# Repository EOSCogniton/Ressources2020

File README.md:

# Ressources2020
Ce Git centralise tous les documents relatifs à la saison 2020 (diapos de Top, documentation, etc)

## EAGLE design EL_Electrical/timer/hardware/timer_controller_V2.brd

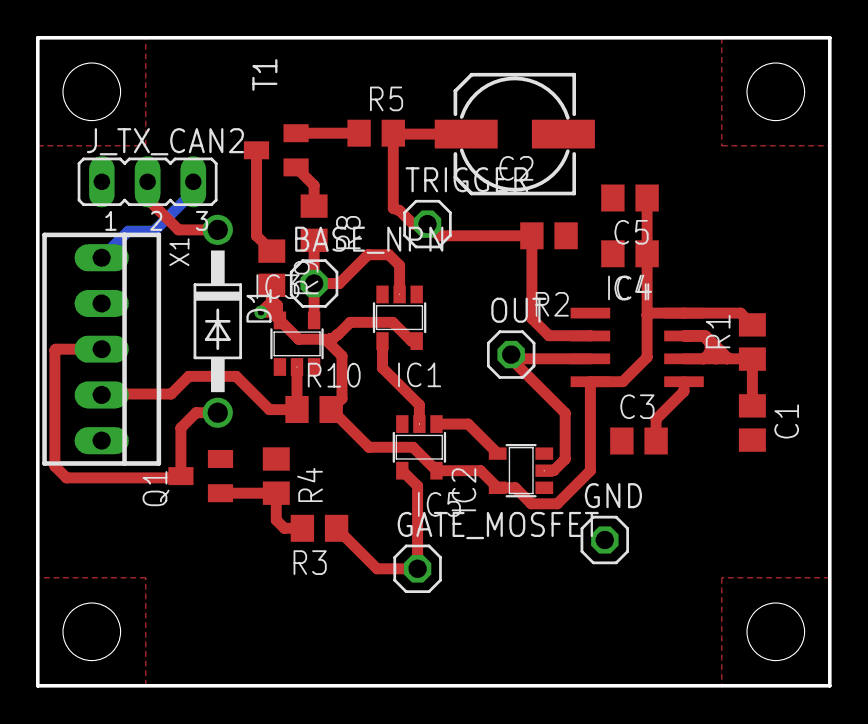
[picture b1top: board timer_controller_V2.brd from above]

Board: 2 copper layers, 44.0 x 36.0 mm, 28 parts (0 on the bottom side), 18 nets.

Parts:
BASE_NPN: BASE_NPN; 1X01
C1: 2.2µF; C0805
C2: 150µF; 153CLV-0605
C3: 0.01µF; C0805
C4: 0.1µF; C0805
C5: 1µF; C0805
D1: 1N4007; DO41-10
GATE_MOSFET: GATE_MOSFET; 1X01
GND: GND; 1X01
IC1, IC2, IC3: TC4S584F; SOT23-5
IC4: LM555D; SO08
IC5: Gate OR; SOT23-5
J_TX_CAN2: JP2
OUT: OUT; 1X01
Q1: BSS138; SOT23
R1: 2.2k; R0805
R2: 18k; R0805
R3, R4: 10k; R0805
R5: 12k; R0805
R8, R9: 100; R0805
R10: 1k; R0805
T1: 2N2369; SOT23
TRIGGER: TRIGGER; 1X01
X1: 22-23-2051

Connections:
12_SWITCHES: J_TX_CAN2.3, X1.1
+12V: C4.1, C5.1, IC1.5, IC2.5, IC3.5, IC4.4, IC4.8, IC5.5, J_TX_CAN2.1, R1.2, R9.2, R10.2, X1.2
BASE_NPN: BASE_NPN.1, IC1.2, IC3.4, R8.2
BP_START: IC3.2, R10.1, X1.4
GATE_MOSFET: GATE_MOSFET.1, IC5.4, R3.1
GND: C1.2, C2.-, C3.1, C4.2, C5.2, GND.1, IC1.3, IC2.3, IC3.3, IC4.1, IC5.3, Q1.2, R2.1, R4.1, X1.5
unnamed: Q1.1, R3.2, R4.2
unnamed: R9.1, T1.3
unnamed: IC1.4, IC5.2
unnamed: IC2.4, IC5.1
unnamed: C3.2, IC4.5
unnamed: C1.1, IC4.6, IC4.7, R1.1
unnamed: R5.1, T1.2
unnamed: R8.1, T1.1
OUT: IC2.2, IC4.3, OUT.1
RELAIS_INJECTEUR_12_PROTEGE: D1.C, J_TX_CAN2.2
RELAIS_INJECTEUR_MASSE: D1.A, Q1.3, X1.3
TRIGGER: C2.+, IC4.2, R2.2, R5.2, TRIGGER.1

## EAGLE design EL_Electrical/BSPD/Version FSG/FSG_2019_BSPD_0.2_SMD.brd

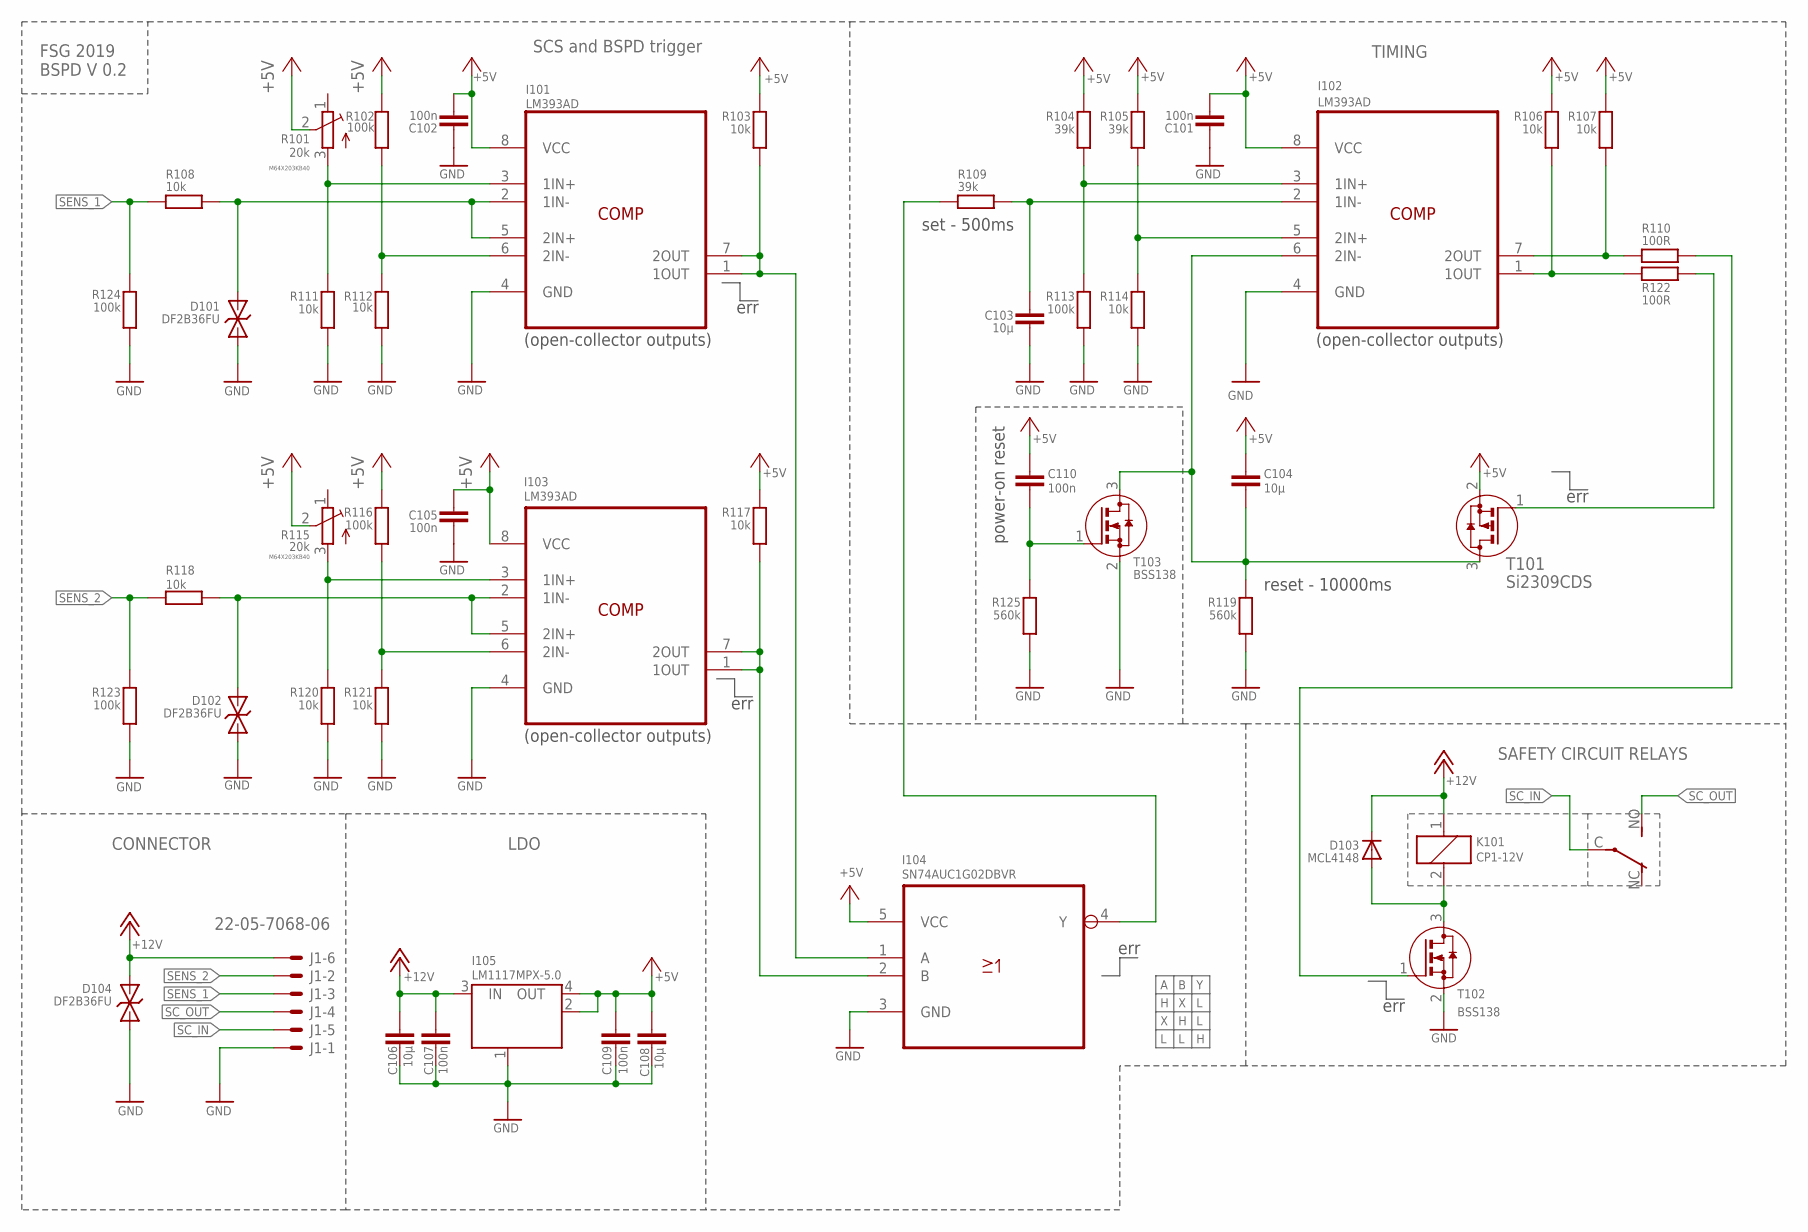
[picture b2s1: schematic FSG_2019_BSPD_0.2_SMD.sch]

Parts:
C101, C102, C105, C107, C109, C110: 100n; C0603
C103, C106, C108: 10µ; C1206
C104: 10µ; C1206K
D101, D102, D104: DF2B36FU; SOD323
D103: MCL4148; MICROMELF
I101, I102, I103: LM393AD; SOIC127P600X175-8N
I104: SN74AUC1G02DBVR; SOT95P280X145-5N
I105: LM1117MPX-5.0; LINEAR_SOT223
J1: 22-05-7068-06; 7395-06
K101: CP1-12V; CP1
R101, R115: 20k; M64X201KB40
R102, R113, R116, R123, R124: 100k; R0603
R103, R106, R107, R108, R111, R112, R114, R117, R118, R120, R121: 10k; R0603
R104, R105, R109: 39k; R0603
R110, R122: 100R; R0603
R119, R125: 560k; R0603
T101: Si2309CDS; SOT-23
T102, T103: BSS138; SOT-23

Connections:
+5V: C101.2, C102.2, C104.1, C105.2, C108.1, C109.2, C110.1, I101.8 (VCC), I102.8 (VCC), I103.8 (VCC), I104.5 (VCC), I105.2 (OUT), I105.4 (OUT), R101.2 (M), R102.1, R103.1, R104.2, R105.2, R106.2, R107.2, R115.2 (M), R116.1, R117.1, T101.2 (S)
+12V: C106.1, C107.1, D103.C, D104.2 (C), I105.3 (IN), J1.6, K101.1
BRAKE_F: D101.2 (C), I101.2 (1IN-), I101.5 (2IN+), R108.2
DF: D102.2 (C), I103.2 (1IN-), I103.5 (2IN+), R118.2
GND: C101.1, C102.1, C103.2, C105.1, C106.2, C107.2, C108.2, C109.1, D101.1 (A), D102.1 (A), D104.1 (A), I101.4 (GND), I102.4 (GND), I103.4 (GND), I104.3 (GND), I105.1 (GND/ADJ), J1.1, R111.2, R112.2, R113.1, R114.1, R119.1, R120.2, R121.2, R123.1, R124.1, R125.1, T102.2 (S), T103.2 (S)
unnamed: I102.5 (2IN+), R105.1, R114.2
unnamed: I103.1 (1OUT), I103.7 (2OUT), I104.2 (B), R117.2
unnamed: I101.1 (1OUT), I101.7 (2OUT), I104.1 (A), R103.2
unnamed: I102.1 (1OUT), R106.1, R122.2
unnamed: C110.2, R125.2, T103.1 (G)
unnamed: I101.3 (1IN+), R101.3 (A), R111.1
unnamed: C104.2, I102.6 (2IN-), R119.2, T101.3 (D), T103.3 (D)
unnamed: I103.3 (1IN+), R115.3 (A), R120.1
unnamed: R110.1, T102.1 (G)
unnamed: D103.A, K101.2, T102.3 (D)
unnamed: C103.1, I102.2 (1IN-), R109.1
unnamed: I102.3 (1IN+), R104.1, R113.2
unnamed: I101.6 (2IN-), R102.2, R112.1
unnamed: I102.7 (2OUT), R107.1, R110.2
unnamed: I103.6 (2IN-), R116.2, R121.1
unnamed: R122.1, T101.1 (G)
unnamed: I104.4 (Y), R109.2
SC_IN: J1.5, K101.C
SC_OUT: J1.4, K101.NO (S)
SENS_1: J1.3, R108.1, R124.2
SENS_2: J1.2, R118.1, R123.2

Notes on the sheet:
COMP
M64X203KB40
FSG 2019 BSPD V 0.2
CONNECTOR
LDO
SAFETY CIRCUIT RELAYS
err
TIMING
SCS and BSPD trigger
power-on reset
set - 500ms
reset - 10000ms
(open-collector outputs)

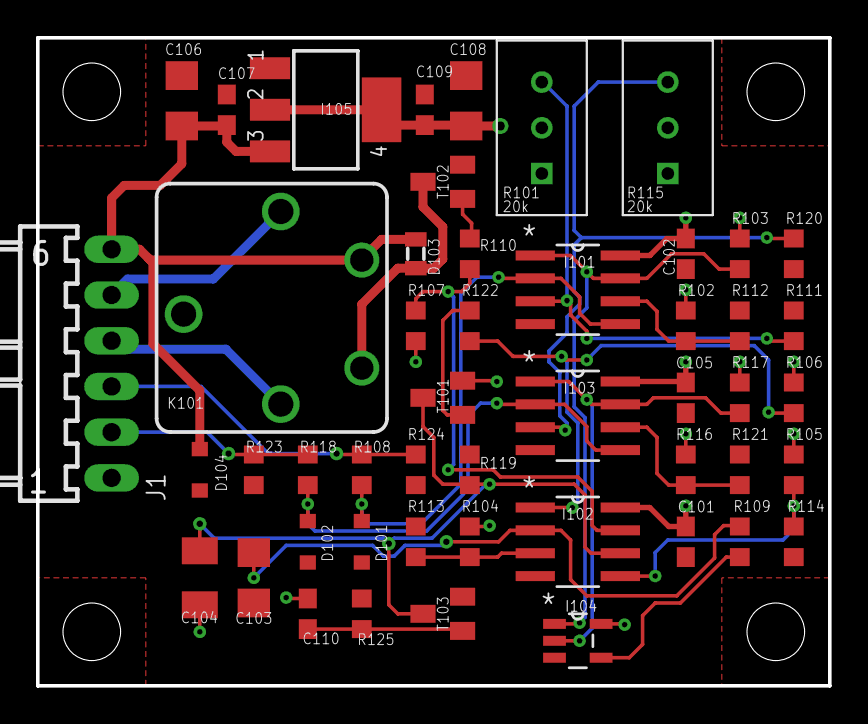
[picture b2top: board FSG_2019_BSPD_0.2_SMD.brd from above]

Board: 2 copper layers, 44.0 x 36.0 mm, 49 parts (0 on the bottom side), 26 nets.

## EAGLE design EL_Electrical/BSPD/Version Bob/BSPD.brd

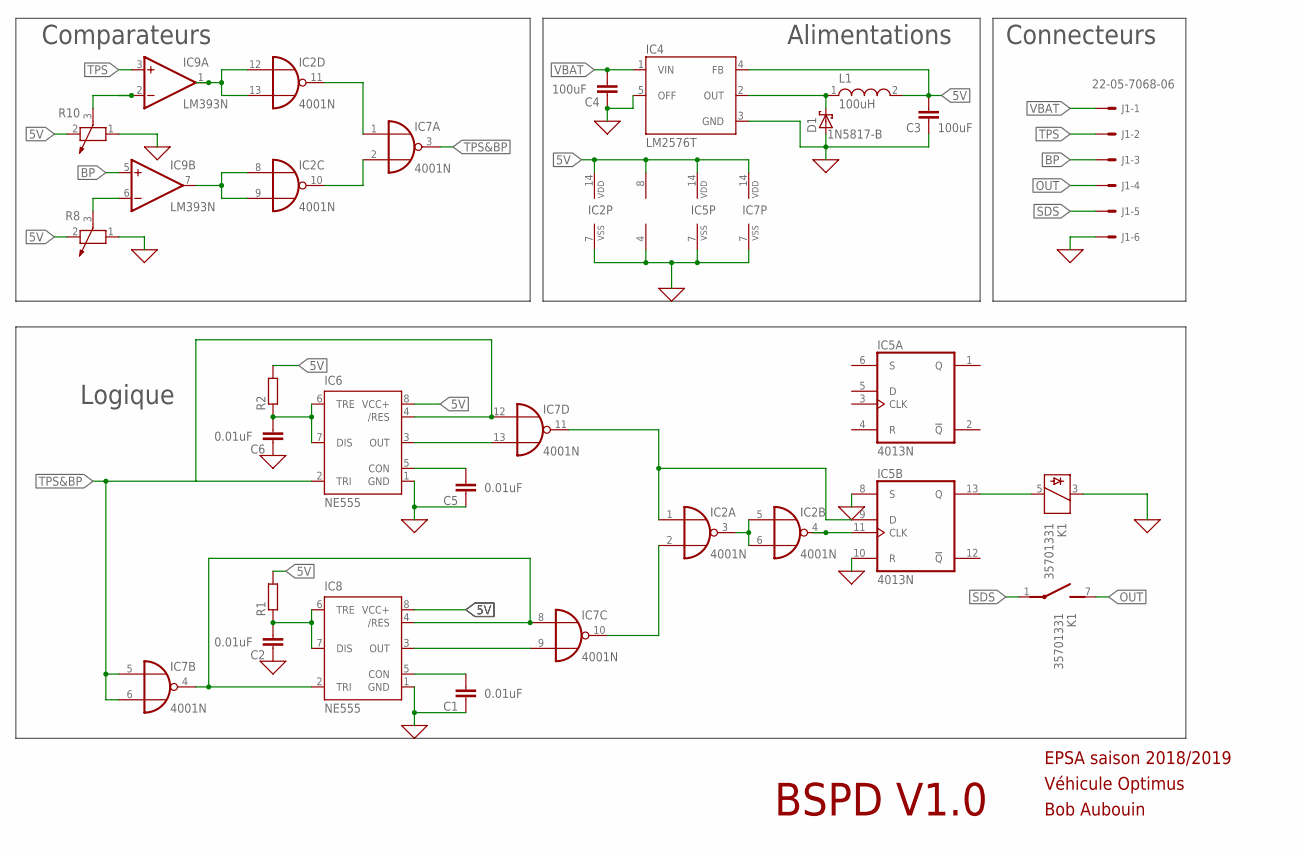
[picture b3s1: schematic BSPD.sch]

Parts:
C1, C2, C5, C6: 0.01uF; C025-025X050
C3, C4: 100uF; C025-025X050
D1: 1N5817-B; DO41-7.6
IC2, IC7: 4001N; DIL14
IC4: LM2576T; TO220-5
IC5: 4013N; DIL14
IC6, IC8: NE555; DIL-08
IC9: LM393N; DIL08
J1: 22-05-7068-06; 7395-06
K1: 35701331; REED
L1: 100uH; WE-TI_8012
R1, R2: R-EU_0207/10; 0207/10
R8, R10: POTENTIOMETER_PT_SPIN; PT-SPIN

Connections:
0: C1.1, C2.1, C3.1, C4.1, C5.1, C6.1, D1.A, IC2.7 (VSS), IC4.3 (GND), IC4.5 (OFF), IC5.7 (VSS), IC5.8 (S), IC5.10 (R), IC6.1 (GND), IC7.7 (VSS), IC8.1 (GND), IC9.4 (V-), J1.6, K1.3, R8.1, R10.1
5V: C3.2, IC2.14 (VDD), IC4.4 (FB), IC5.14 (VDD), IC6.8 (VCC+), IC7.14 (VDD), IC8.8 (VCC+), IC9.8 (V+), L1.2, R1.2, R2.2, R8.2, R10.2
BP: IC9.5 (+IN), J1.3
unnamed: C1.2, IC8.5 (CON)
unnamed: IC7.4 (O), IC7.8 (I0), IC8.2 (TRI), IC8.4 (/RES)
unnamed: C2.2, IC8.6 (TRE), IC8.7 (DIS), R1.1
unnamed: IC7.9 (I1), IC8.3 (OUT)
unnamed: C6.2, IC6.6 (TRE), IC6.7 (DIS), R2.1
unnamed: C5.2, IC6.5 (CON)
unnamed: IC2.12 (I0), IC2.13 (I1), IC9.1 (OUT)
unnamed: IC2.2 (I1), IC7.10 (O)
unnamed: IC2.1 (I0), IC5.9 (D), IC7.11 (O)
unnamed: IC2.4 (O), IC5.11 (CLK)
unnamed: IC6.3 (OUT), IC7.13 (I1)
unnamed: IC5.13 (Q), K1.5
unnamed: IC9.2 (-IN), R10.3
unnamed: IC9.6 (-IN), R8.3
unnamed: IC2.8 (I0), IC2.9 (I1), IC9.7 (OUT)
unnamed: D1.C, IC4.2 (OUT), L1.1
unnamed: IC2.11 (O), IC7.1 (I0)
unnamed: IC2.10 (O), IC7.2 (I1)
unnamed: IC2.3 (O), IC2.5 (I0), IC2.6 (I1)
OUT: J1.4, K1.7 (S)
SDS: J1.5, K1.1
TPS: IC9.3 (+IN), J1.2
TPS&BP: IC6.2 (TRI), IC6.4 (/RES), IC7.3 (O), IC7.5 (I0), IC7.6 (I1), IC7.12 (I0)
VBAT: C4.2, IC4.1 (VIN), J1.1

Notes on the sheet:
BSPD V1.0
EPSA saison 2018/2019
Véhicule Optimus
Bob Aubouin
Logique
Comparateurs
Alimentations
Connecteurs

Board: 2 copper layers, 21 parts (0 on the bottom side), 27 nets, no tracks yet.

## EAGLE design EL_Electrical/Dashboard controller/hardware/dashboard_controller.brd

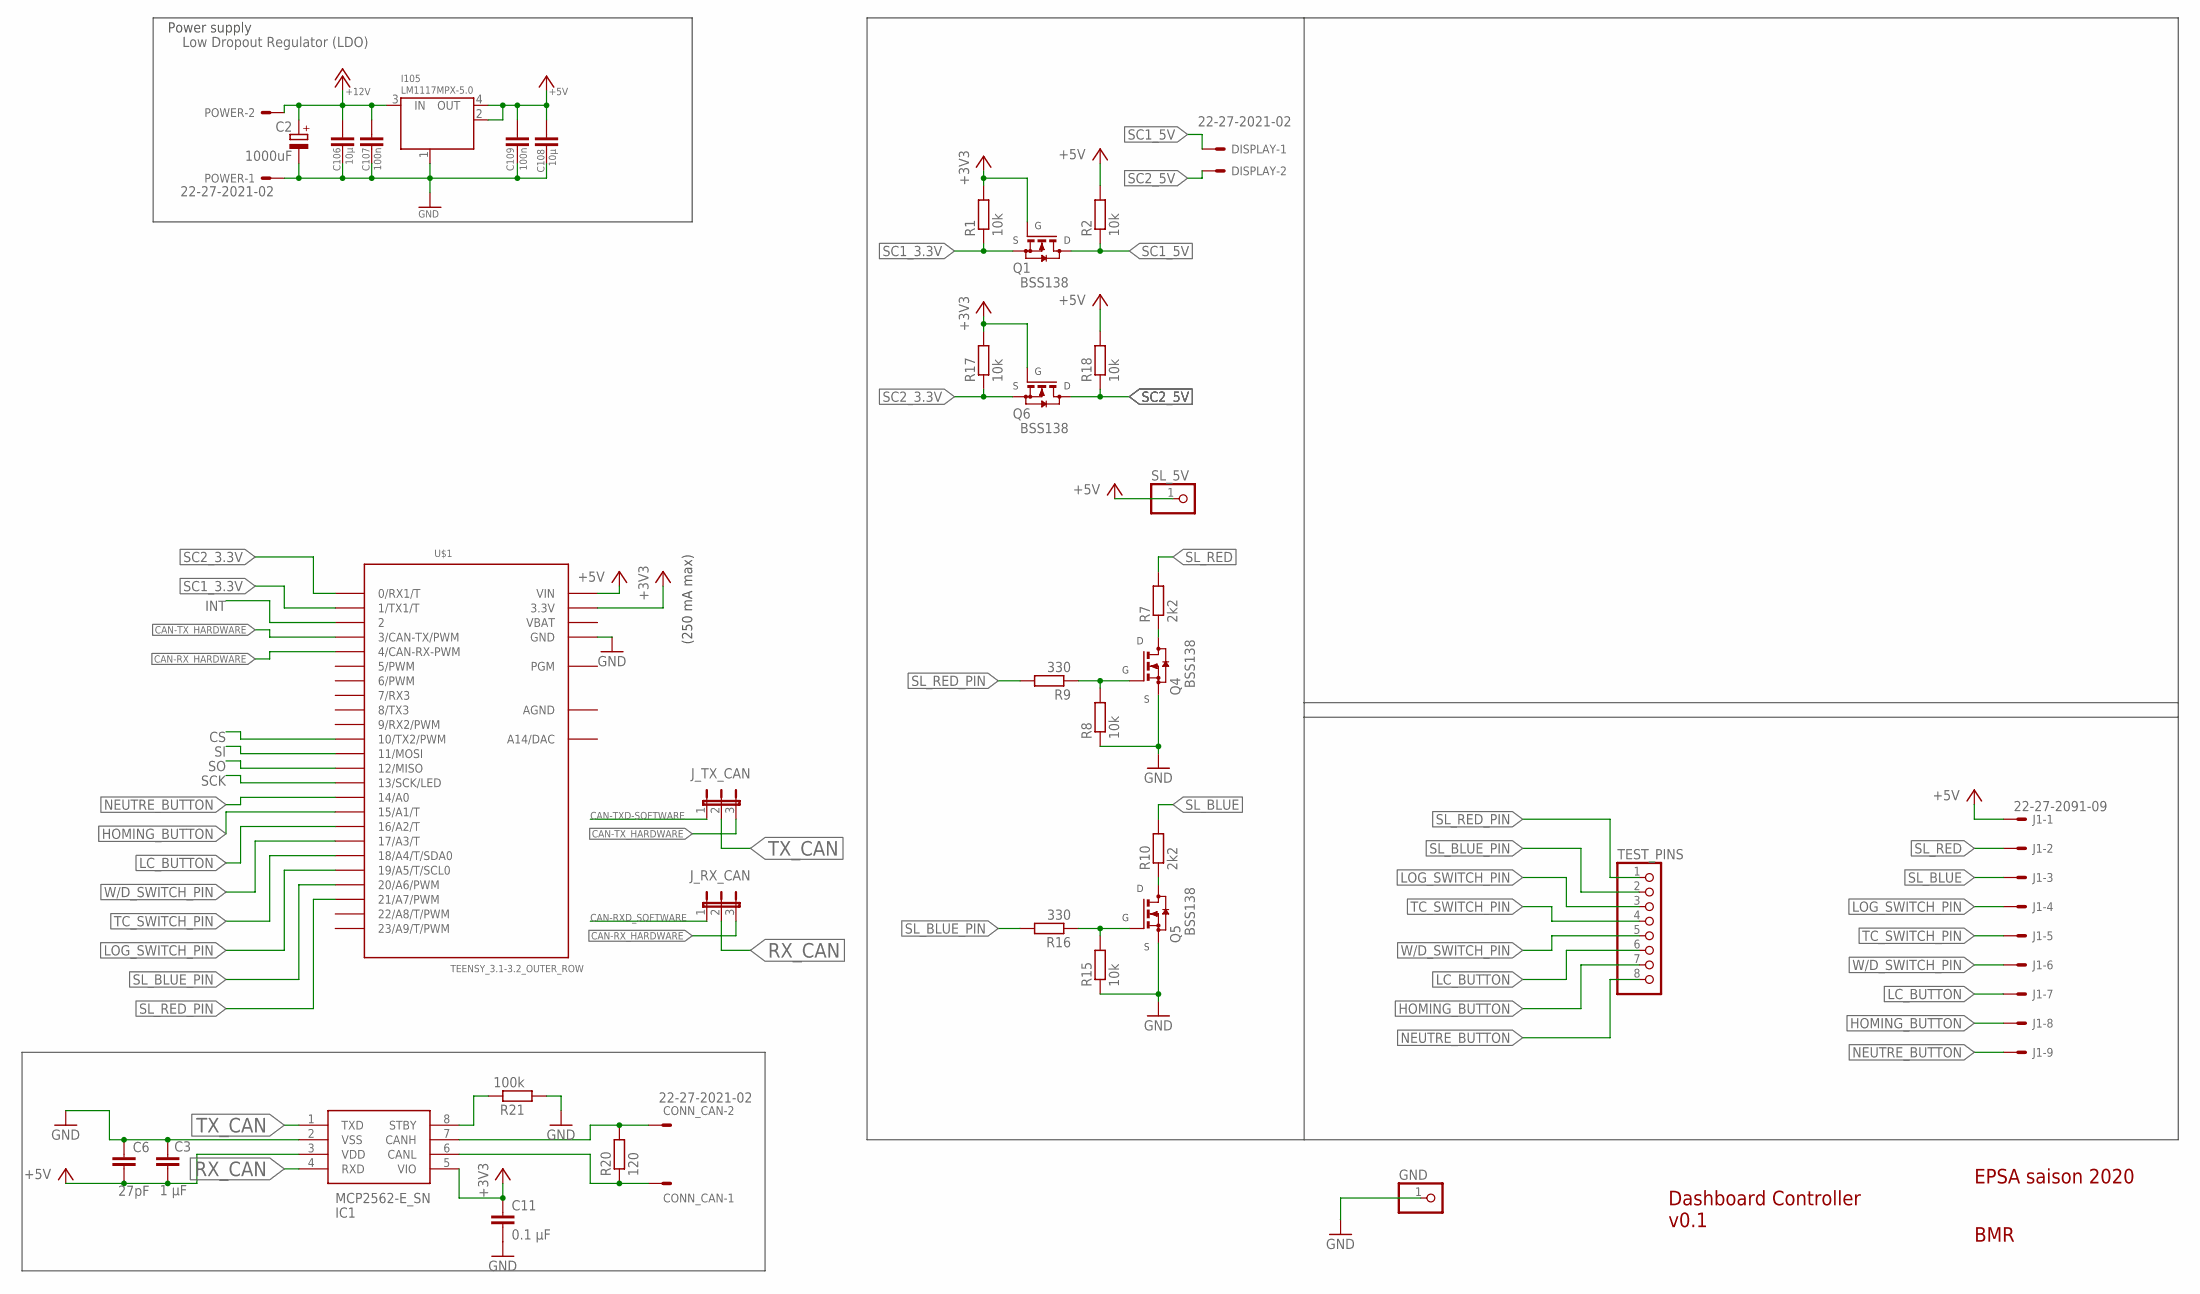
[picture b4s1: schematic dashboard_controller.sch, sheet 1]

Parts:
C2: 1000uF; E25-10
C3: 1 µF; C0805
C6: 27pF; C0805
C11: 0.1 µF; C0805
C106, C108: 10µ; C0805
C107, C109: 100n; C0603
CONN_CAN: 22-27-2021-02; 6410-02
DISPLAY: 22-27-2021-02; 6410-02
GND: PINHD-1X1; 1X01
I105: LM1117MPX-5.0; LINEAR_SOT223
IC1: MCP2562-E_SN; SOIC127P600X175-8N
J1: 22-27-2091-09; 6410-09
J_RX_CAN: JP2E; JP2
J_TX_CAN: JP2E; JP2
POWER: 22-27-2021-02; 6410-02
Q1, Q4, Q5, Q6: BSS138; SOT23
R1, R2, R8, R15, R17, R18: 10k; R0805
R7, R10: 2k2; R0805
R9, R16: 330; R0805
R20: 120; R0805
R21: 100k; R0805
SL_5V: PINHD-1X1; 1X01
TEST_PINS: PINHD-1X8; 1X08
U$1: TEENSY_3.1-3.2_OUTER_ROW; TEENSY_3.0-3.2&LC_OUTER_ROW

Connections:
+3V3: C11.1, IC1.5 (VIO), Q1.1 (G), Q6.1 (G), R1.2, R17.2, U$1.3.3V, U$1.3.3V1 (3.3V); also elsewhere on the board
+5V: C3.2, C6.2, C108.1, C109.2, I105.2 (OUT), I105.4 (OUT), IC1.3 (VDD), J1.1, R2.2, R18.2, SL_5V.1, U$1.VIN
+12V: C2.+, C106.1, C107.1, I105.3 (IN), POWER.2
AGND: U$1.AGND
CAN-RXD_SOFTWARE: J_RX_CAN.1; also elsewhere on the board
CAN-RX_HARDWARE: J_RX_CAN.3, U$1.4 (4/CAN-RX-PWM)
CAN-TXD-SOFTWARE: J_TX_CAN.1; also elsewhere on the board
CAN-TX_HARDWARE: J_TX_CAN.3, U$1.3 (3/CAN-TX/PWM)
CS: U$1.10 (10/TX2/PWM); also elsewhere on the board
GND: C2.-, C3.1, C6.1, C11.2, C106.2, C107.2, C108.2, C109.1, GND.1, I105.1 (GND/ADJ), IC1.2 (VSS), POWER.1, Q4.2 (S), Q5.2 (S), R8.1, R15.1, R21.1, U$1.GND, U$1.GND1 (GND); also elsewhere on the board
HOMING_BUTTON: J1.8, TEST_PINS.7, U$1.15/A1 (15/A1/T)
INT: U$1.2; also elsewhere on the board
LC_BUTTON: J1.7, TEST_PINS.6, U$1.16/A2 (16/A2/T)
LOG_SWITCH_PIN: J1.4, TEST_PINS.3, U$1.19/A5 (19/A5/T/SCL0)
unnamed: CONN_CAN.2, IC1.7 (CANH), R20.2
unnamed: IC1.8 (STBY), R21.2
unnamed: Q4.3 (D), R7.1
unnamed: Q5.1 (G), R15.2, R16.1
unnamed: CONN_CAN.1, IC1.6 (CANL), R20.1
unnamed: Q4.1 (G), R8.2, R9.1
unnamed: Q5.3 (D), R10.1
NEUTRE_BUTTON: J1.9, TEST_PINS.8, U$1.14/A0
RX_CAN: IC1.4 (RXD), J_RX_CAN.2
SC1_3.3V: Q1.2 (S), R1.1, U$1.1 (1/TX1/T)
SC1_5V: DISPLAY.1, Q1.3 (D), R2.1
SC2_3.3V: Q6.2 (S), R17.1, U$1.0 (0/RX1/T)
SC2_5V: DISPLAY.2, Q6.3 (D), R18.1
SCK: U$1.13 (13/SCK/LED); also elsewhere on the board
SI: U$1.11 (11/MOSI); also elsewhere on the board
SL_BLUE: J1.3, R10.2
SL_BLUE_PIN: R16.2, TEST_PINS.2, U$1.20/A6 (20/A6/PWM)
SL_RED: J1.2, R7.2
SL_RED_PIN: R9.2, TEST_PINS.1, U$1.21/A7 (21/A7/PWM)
SO: U$1.12 (12/MISO); also elsewhere on the board
TC_SWITCH_PIN: J1.5, TEST_PINS.4, U$1.18/A4 (18/A4/T/SDA0)
TX_CAN: IC1.1 (TXD), J_TX_CAN.2
VBAT: U$1.VBAT
W/D_SWITCH_PIN: J1.6, TEST_PINS.5, U$1.17/A3 (17/A3/T)

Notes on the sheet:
Dashboard Controller v0.1
EPSA saison 2020
BMR
(250 mA max)
Low Dropout Regulator (LDO)
Power supply

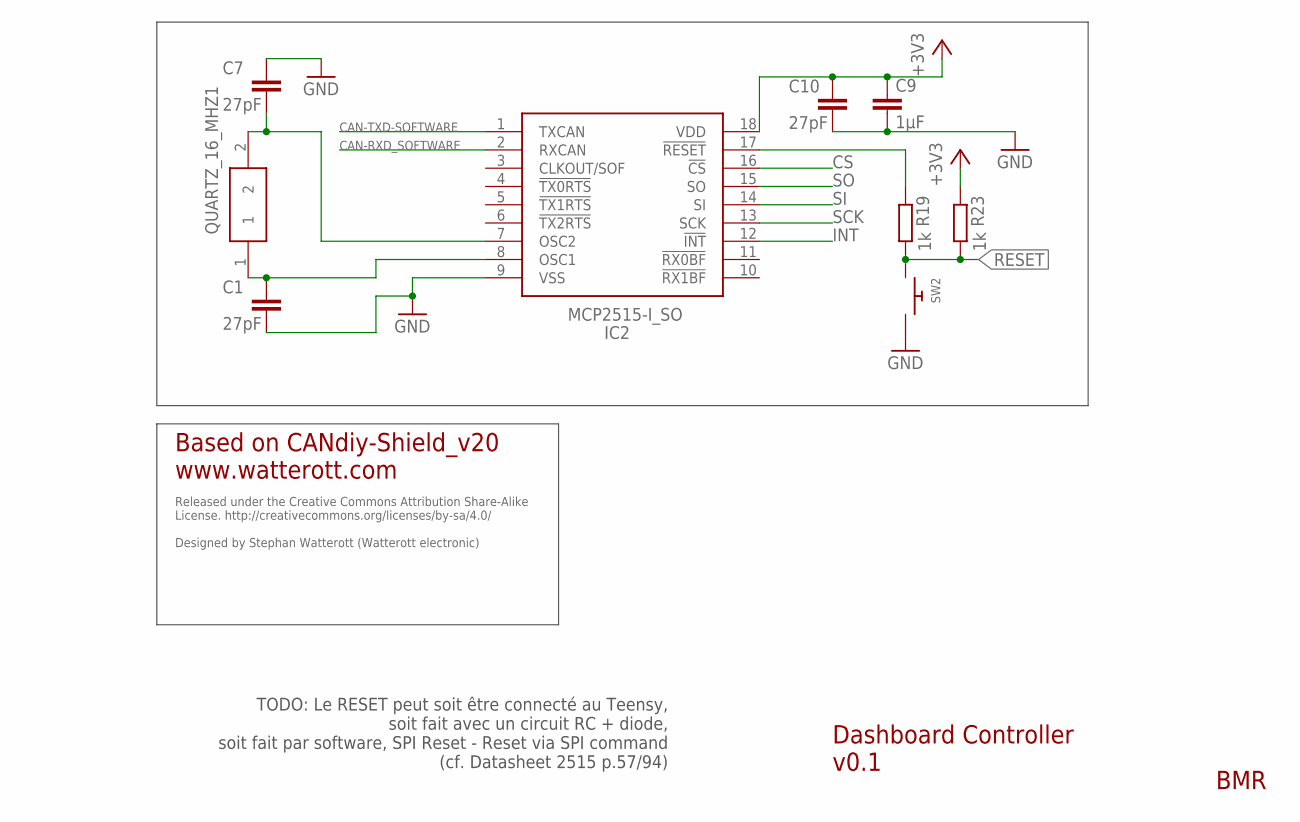
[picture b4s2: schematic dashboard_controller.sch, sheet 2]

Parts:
C1, C7, C10: 27pF; C0805
C9: 1µF; C0805
IC2: MCP2515-I_SO; SOIC127P1030X265-18N
QUARTZ_16_MHZ1: FOXSLF_160-20; HC49SLF_1
R19, R23: 1k; R0805
SW2: SWITCH_PUSHBUTTONEVQ-PE; TACT_PANA-EVQ

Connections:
+3V3: C9.1, C10.1, IC2.18 (VDD), R23.1; also elsewhere on the board
CAN-RXD_SOFTWARE: IC2.2 (RXCAN); also elsewhere on the board
CAN-TXD-SOFTWARE: IC2.1 (TXCAN); also elsewhere on the board
CS: IC2.16 (!CS); also elsewhere on the board
GND: C1.2, C7.1, C9.2, C10.2, IC2.9 (VSS), SW2.P$2; also elsewhere on the board
INT: IC2.12 (!INT); also elsewhere on the board
unnamed: C1.1, IC2.8 (OSC1), QUARTZ_16_MHZ1.1
unnamed: C7.2, IC2.7 (OSC2), QUARTZ_16_MHZ1.2
unnamed: IC2.17 (!RESET), R19.1
RESET: R19.2, R23.2, SW2.P$1
SCK: IC2.13 (SCK); also elsewhere on the board
SI: IC2.14 (SI); also elsewhere on the board
SO: IC2.15 (SO); also elsewhere on the board

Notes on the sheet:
Dashboard Controller v0.1
BMR
Released under the Creative Commons Attribution Share-Alike License. http://creativecommons.org/licenses/by-sa/4.0/ Designed by Stephan Watterott (Watterott electronic)
Based on CANdiy-Shield_v20 www.watterott.com
TODO: Le RESET peut soit être connecté au Teensy, soit fait avec un circuit RC + diode, soit fait par software, SPI Reset - Reset via SPI command (cf. Datasheet 2515 p.57/94)

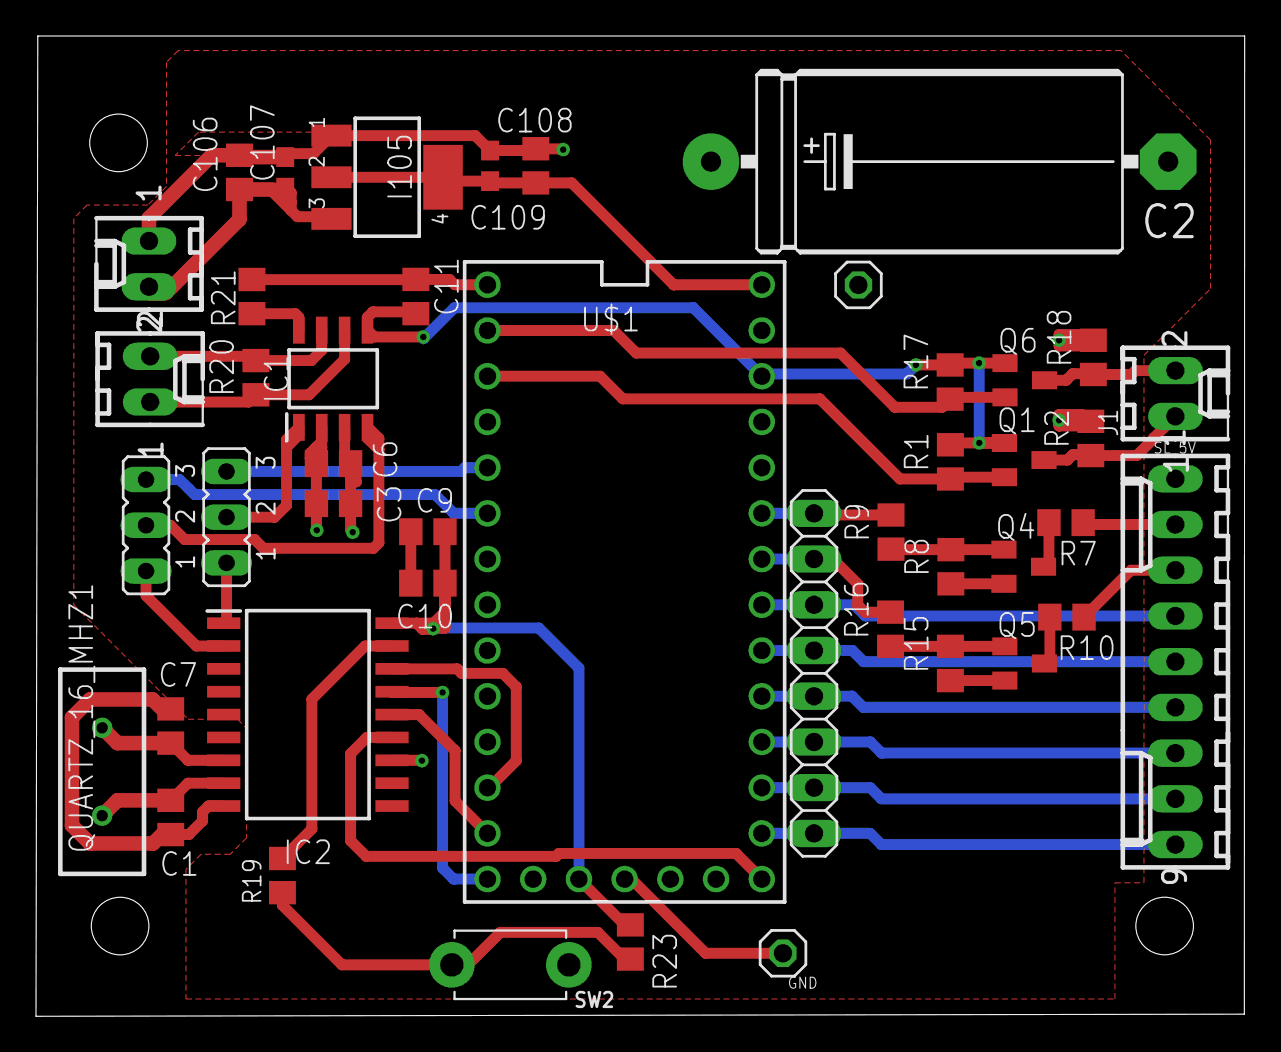
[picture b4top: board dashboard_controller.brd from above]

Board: 4 copper layers, 67.1 x 54.5 mm, 45 parts (0 on the bottom side), 40 nets.

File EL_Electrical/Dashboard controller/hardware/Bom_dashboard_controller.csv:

Qty;Value;Device;Package;Parts;Description;ALLIED_NUMBER;CASE;DESCRIPTION;HEIGHT;MANUFACTURER_NAME;MANUFACTURER_PART_NUMBER;MF;MONTHLY_USAGE;MPN;OC_FARNELL;OC_NEWARK;PART_NUMBER;POPULARITY;PRICE;RS_PART_NUMBER;SPICEPREFIX;SUPPLIER;TYPE;VALUE
2;;JP2E;JP2;J_RX_CAN, J_TX_CAN;JUMPER;;;;;;;;;;;;;34;;;;;;
2;;PINHD-1X1;1X01;GND, SL_5V;PIN HEADER;;;;;;;;;;;;;64;;;;;;
1;;PINHD-1X2;1X02;TEST_CAN;PIN HEADER;;;;;;;;;;;;;98;;;;;;
1;;PINHD-1X8;1X08;TEST_PINS;PIN HEADER;;;;;;;;;;;;;67;;;;;;
1;;SWITCH_PUSHBUTTONEVQ-PE;TACT_PANA-EVQ;SW2;Buttons;;;;;;;;;;;;;;;;;;;
1;0.1 µF;C-EUC0805;C0805;C11;CAPACITOR, European symbol;;;;;;;;;;;;;88;;;C;;;
1;1 µF;C-EUC0805;C0805;C3;CAPACITOR, European symbol;;;;;;;;;;;;;88;;;C;;;
1;1000uF;CPOL-EUE25-10AXIAL;E25-10;C2;POLARIZED CAPACITOR, European symbol;;;;;;;;;;;;;0;;;C;;;
1;100k;R-EU_R0805;R0805;R21;RESISTOR, European symbol;;;;;;;;;;;;;86;;;R;;;
2;100n;C-EUC0603;C0603;C107, C109;CAPACITOR, European symbol;;;;;;;;;;;;;;;;;;;
6;10k;R-EU_R0805;R0805;R1, R2, R8, R15, R17, R18;RESISTOR, European symbol;;;;;;;;;;;;;86;;;R;;;
2;10µ;C-EUC0805;C0805;C106, C108;CAPACITOR, European symbol;;;;;;;;;;;;;88;;;C;;;
1;120;R-EU_R0805;R0805;R20;RESISTOR, European symbol;;;;;;;;;;;;;86;;;R;;;
2;1k;R-EU_R0805;R0805;R19, R23;RESISTOR, European symbol;;;;;;;;;;;;;86;;;R;;;
1;1µF;C-EUC0805;C0805;C9;CAPACITOR, European symbol;;;;;;;;;;;;;88;;;C;;;
3;22-27-2021-02;22-27-2021-02;6410-02;ALIM, CONN_CAN, DISPLAY;CONNECTOR;;;;;;;MOLEX;;;unknown;unknown;;0;;;;;;
1;22-27-2091-09;22-27-2091-09;6410-09;J1;CONNECTOR;;;;;;;MOLEX;;;unknown;unknown;;0;;;;;;
4;27pF;C-EUC0805;C0805;C1, C6, C7, C10;CAPACITOR, European symbol;;;;;;;;;;;;;88;;;C;;;
2;2k2;R-EU_R0805;R0805;R7, R10;RESISTOR, European symbol;;;;;;;;;;;;;86;;;R;;;
2;330;R-EU_R0805;R0805;R9, R16;RESISTOR, European symbol;;;;;;;;;;;;;86;;;R;;;
4;BSS138;BSS123;SOT23;Q1, Q4, Q5, Q6;N-CHANNEL MOS FET;;;;;;;;;;;;;21;;;;;;
1;FOXSLF_160-20;FOXSLF_160-20;HC49SLF_1;QUARTZ_16_MHZ1;Crystal 16.000MHz HC49S HC-49-SLF Crystal 16MHz, ??30ppm, 2-Pin;;;Crystal 16.000MHz HC49S HC-49-SLF Crystal 16MHz, ??30ppm, 2-Pin;mm;Fox;FOXSLF/160-20;;;;;;;;;1734298;;;;
1;LM1117MPX-5.0;0022_LM1117IMPX-5.0;LINEAR_SOT223;I105;Low-dropout linear regulator 5V  -LM1117IMPX-5.0;;SOT223;;;;;;_____;;;;LM1117IMPX-5.0;;_____;;;_____;Circuito_Integrato;LM1117IMPX-5.0
1;MCP2515-I_SO;MCP2515-I_SO;SOIC127P1030X265-18N;IC2;CAN Controller SPI data filtering SO18;70045399;;CAN Controller SPI data filtering SO18;2.65mm;Microchip;MCP2515-I/SO;;;;;;;;;1445765;;;;
1;MCP2562-E_SN;MCP2562-E_SN;SOIC127P600X175-8N;IC1;CAN Transceiver 1Mbps 5V 125degC SOIC8 CAN Transceiver 1MBps IEC 61000-4-2 Standby-Mode 8pins SOIC;70415107;;CAN Transceiver 1Mbps 5V 125degC SOIC8 CAN Transceiver 1MBps IEC 61000-4-2 Standby-Mode 8pins SOIC;1.75mm;Microchip;MCP2562-E/SN;;;;;;;;;7990228P;;;;
1;TEENSY_3.1-3.2_OUTER_ROW;TEENSY_3.1-3.2_OUTER_ROW;TEENSY_3.0-3.2&LC_OUTER_ROW;U$1;Footprint for Teensy 3.1 or 3.2 board using all pin connections on the outer perimeter;;;;;;;;;;;;;;;;;;;

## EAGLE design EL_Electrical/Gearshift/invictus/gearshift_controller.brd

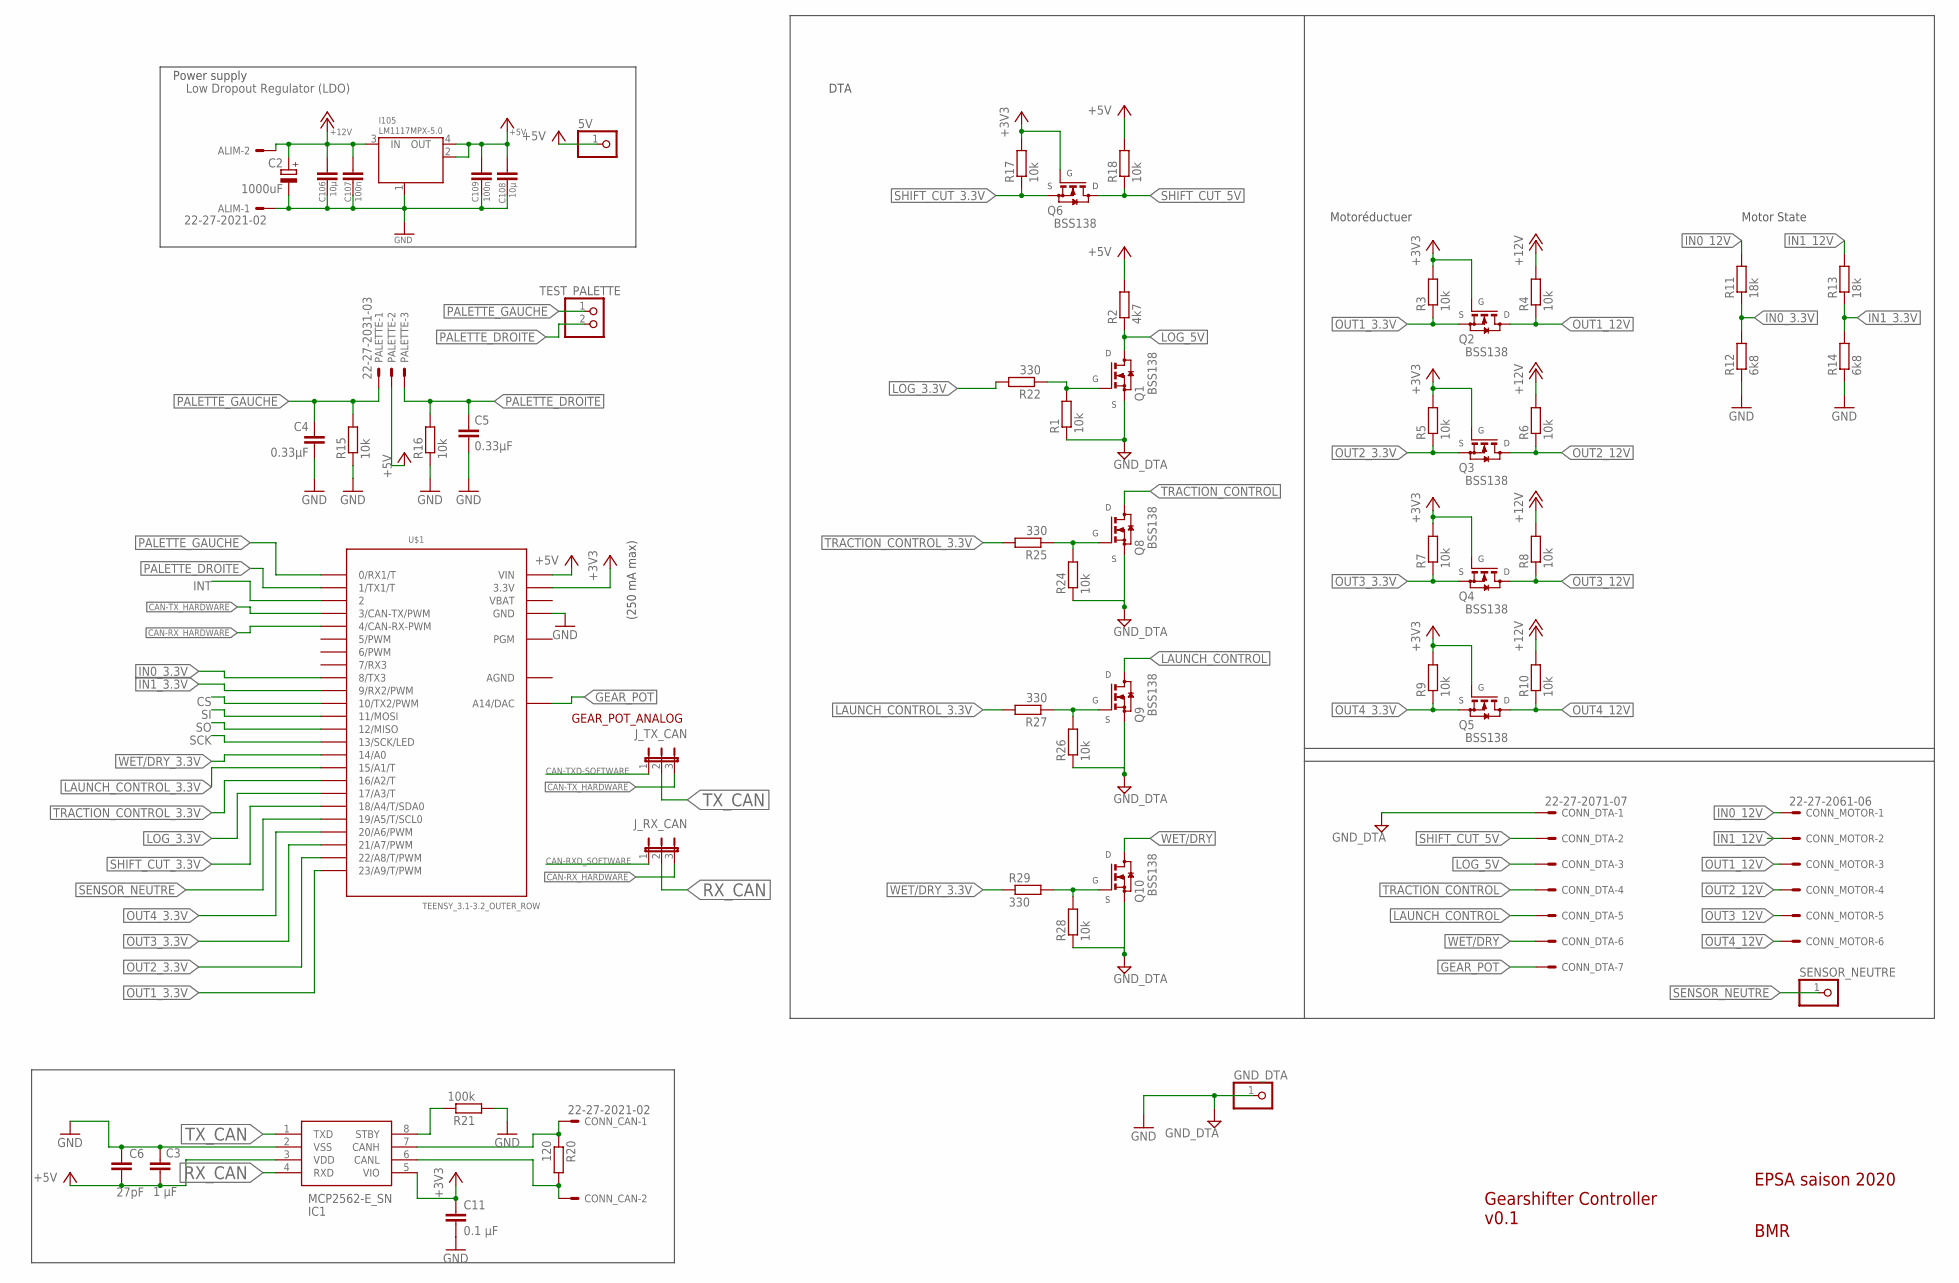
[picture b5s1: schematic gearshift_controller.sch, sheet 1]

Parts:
5V: PINHD-1X1; 1X01
ALIM: 22-27-2021-02; 6410-02
C2: 1000uF; E25-10
C3: 1 µF; C0805
C4, C5: 0.33µF; C0805
C6: 27pF; C0805
C11: 0.1 µF; C0805
C106, C108: 10µ; C0805
C107, C109: 100n; C0603
CONN_CAN: 22-27-2021-02; 6410-02
CONN_DTA: 22-27-2071-07; 6410-07
CONN_MOTOR: 22-27-2061-06; 6410-06
GND_DTA: PINHD-1X1; 1X01
I105: LM1117MPX-5.0; LINEAR_SOT223
IC1: MCP2562-E_SN; SOIC127P600X175-8N
J_RX_CAN: JP2E; JP2
J_TX_CAN: JP2E; JP2
PALETTE: 22-27-2031-03; 6410-03
Q1, Q2, Q3, Q4, Q5, Q6, Q8, Q9, Q10: BSS138; SOT23
R1, R3, R4, R5, R6, R7, R8, R9, R10, R15, R16, R17, R18, R24, R26, R28: 10k; R0805
R2: 4k7; R0805
R11, R13: 18k; R0805
R12, R14: 6k8; R0805
R20: 120; R0805
R21: 100k; R0805
R22, R25, R27, R29: 330; R0805
SENSOR_NEUTRE: PINHD-1X1; 1X01
TEST_PALETTE: PINHD-1X2; 1X02
U$1: TEENSY_3.1-3.2_OUTER_ROW; TEENSY_3.0-3.2&LC_OUTER_ROW

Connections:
+3V3: C11.1, IC1.5 (VIO), Q2.1 (G), Q3.1 (G), Q4.1 (G), Q5.1 (G), Q6.1 (G), R3.2, R5.2, R7.2, R9.2, R17.2, U$1.3.3V, U$1.3.3V1 (3.3V); also elsewhere on the board
+5V: 5V.1, C3.2, C6.2, C108.1, C109.2, I105.2 (OUT), I105.4 (OUT), IC1.3 (VDD), PALETTE.2, R2.2, R18.2, U$1.VIN
+12V: ALIM.2, C2.+, C106.1, C107.1, I105.3 (IN), R4.2, R6.2, R8.2, R10.2
AGND: U$1.AGND
CAN-RXD_SOFTWARE: J_RX_CAN.1; also elsewhere on the board
CAN-RX_HARDWARE: J_RX_CAN.3, U$1.4 (4/CAN-RX-PWM)
CAN-TXD-SOFTWARE: J_TX_CAN.1; also elsewhere on the board
CAN-TX_HARDWARE: J_TX_CAN.3, U$1.3 (3/CAN-TX/PWM)
CS: U$1.10 (10/TX2/PWM); also elsewhere on the board
GEAR_POT: CONN_DTA.7, U$1.RESET/DAC (A14/DAC)
GND: ALIM.1, C2.-, C3.1, C4.2, C5.2, C6.1, C11.2, C106.2, C107.2, C108.2, C109.1, CONN_DTA.1, GND_DTA.1, I105.1 (GND/ADJ), IC1.2 (VSS), Q1.2 (S), Q8.2 (S), Q9.2 (S), Q10.2 (S), R1.1, R12.1, R14.1, R15.1, R16.1, R21.1, R24.1, R26.1, R28.1, U$1.GND, U$1.GND1 (GND); also elsewhere on the board
IN0_3.3V: R11.1, R12.2, U$1.8 (8/TX3)
IN0_12V: CONN_MOTOR.1, R11.2
IN1_3.3V: R13.1, R14.2, U$1.9 (9/RX2/PWM)
IN1_12V: CONN_MOTOR.2, R13.2
INT: U$1.2; also elsewhere on the board
LAUNCH_CONTROL: CONN_DTA.5, Q9.3 (D)
LAUNCH_CONTROL_3.3V: R27.2, U$1.15/A1 (15/A1/T)
LOG_3.3V: R22.2, U$1.17/A3 (17/A3/T)
LOG_5V: CONN_DTA.3, Q1.3 (D), R2.1
unnamed: Q1.1 (G), R1.2, R22.1
unnamed: IC1.8 (STBY), R21.2
unnamed: CONN_CAN.1, IC1.7 (CANH), R20.1
unnamed: CONN_CAN.2, IC1.6 (CANL), R20.2
unnamed: Q8.1 (G), R24.2, R25.1
unnamed: Q9.1 (G), R26.2, R27.1
unnamed: Q10.1 (G), R28.2, R29.2
OUT1_3.3V: Q2.2 (S), R3.1, U$1.23/A9 (23/A9/T/PWM)
OUT1_12V: CONN_MOTOR.3, Q2.3 (D), R4.1
OUT2_3.3V: Q3.2 (S), R5.1, U$1.22/A8 (22/A8/T/PWM)
OUT2_12V: CONN_MOTOR.4, Q3.3 (D), R6.1
OUT3_3.3V: Q4.2 (S), R7.1, U$1.21/A7 (21/A7/PWM)
OUT3_12V: CONN_MOTOR.5, Q4.3 (D), R8.1
OUT4_3.3V: Q5.2 (S), R9.1, U$1.20/A6 (20/A6/PWM)
OUT4_12V: CONN_MOTOR.6, Q5.3 (D), R10.1
PALETTE_DROITE: C5.1, PALETTE.3, R16.2, TEST_PALETTE.2, U$1.1 (1/TX1/T)
PALETTE_GAUCHE: C4.1, PALETTE.1, R15.2, TEST_PALETTE.1, U$1.0 (0/RX1/T)
RX_CAN: IC1.4 (RXD), J_RX_CAN.2
SCK: U$1.13 (13/SCK/LED); also elsewhere on the board
SENSOR_NEUTRE: SENSOR_NEUTRE.1, U$1.19/A5 (19/A5/T/SCL0)
SHIFT_CUT_3.3V: Q6.2 (S), R17.1, U$1.18/A4 (18/A4/T/SDA0)
SHIFT_CUT_5V: CONN_DTA.2, Q6.3 (D), R18.1
SI: U$1.11 (11/MOSI); also elsewhere on the board
SO: U$1.12 (12/MISO); also elsewhere on the board
TRACTION_CONTROL: CONN_DTA.4, Q8.3 (D)
TRACTION_CONTROL_3.3V: R25.2, U$1.16/A2 (16/A2/T)
TX_CAN: IC1.1 (TXD), J_TX_CAN.2
VBAT: U$1.VBAT
WET/DRY: CONN_DTA.6, Q10.3 (D)
WET/DRY_3.3V: R29.1, U$1.14/A0

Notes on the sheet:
Motor State
Gearshifter Controller v0.1
EPSA saison 2020
BMR
(250 mA max)
Low Dropout Regulator (LDO)
GEAR_POT_ANALOG
Power supply
DTA
Motoréductuer

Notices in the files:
parts and their libraries:
wurth_elektronik_passive_rev16d: Copyright: Würth Elektronik
